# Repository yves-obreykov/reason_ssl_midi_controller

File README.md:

# Reason SSL midi-controller
This project aims to design a custom Midi controller for controlling the SSL-mixer (EQ and Compressor) in Reason DAW

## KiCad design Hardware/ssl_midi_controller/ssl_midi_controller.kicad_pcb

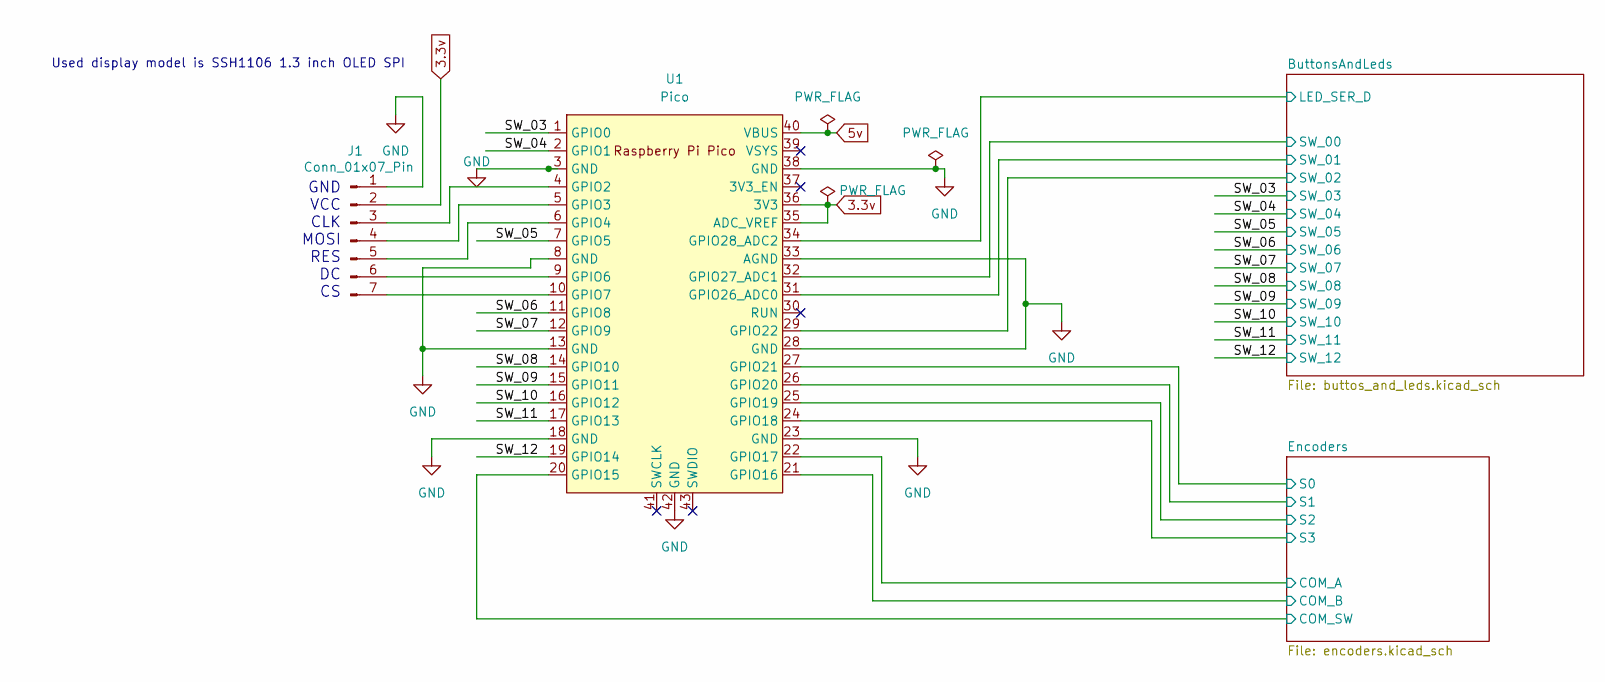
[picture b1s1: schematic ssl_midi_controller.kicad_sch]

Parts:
J1: Conn_01x07_Pin; PinHeader_1x07_P2.54mm_Vertical
U1: Pico; RaspberryPi_Pico_Common_THT

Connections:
3.3v: J1.2, U1.35 (ADC_VREF), U1.36 (3V3); also elsewhere on the board
5v: U1.40 (VBUS); also elsewhere on the board
/ButtonsAndLeds/LED_SER_D: U1.34 (GPIO28_ADC2); also elsewhere on the board
/ButtonsAndLeds/SW_00: U1.32 (GPIO27_ADC1); also elsewhere on the board
/ButtonsAndLeds/SW_01: U1.31 (GPIO26_ADC0); also elsewhere on the board
/ButtonsAndLeds/SW_02: U1.29 (GPIO22); also elsewhere on the board
/Encoders/COM_A: U1.22 (GPIO17); also elsewhere on the board
/Encoders/COM_B: U1.21 (GPIO16); also elsewhere on the board
/Encoders/COM_SW: U1.20 (GPIO15); also elsewhere on the board
/Encoders/S0: U1.27 (GPIO21); also elsewhere on the board
/Encoders/S1: U1.26 (GPIO20); also elsewhere on the board
/Encoders/S2: U1.25 (GPIO19); also elsewhere on the board
/Encoders/S3: U1.24 (GPIO18); also elsewhere on the board
/SW_03: U1.1 (GPIO0); also elsewhere on the board
/SW_04: U1.2 (GPIO1); also elsewhere on the board
/SW_05: U1.7 (GPIO5); also elsewhere on the board
/SW_06: U1.11 (GPIO8); also elsewhere on the board
/SW_07: U1.12 (GPIO9); also elsewhere on the board
/SW_08: U1.14 (GPIO10); also elsewhere on the board
/SW_09: U1.15 (GPIO11); also elsewhere on the board
/SW_10: U1.16 (GPIO12); also elsewhere on the board
/SW_11: U1.17 (GPIO13); also elsewhere on the board
/SW_12: U1.19 (GPIO14); also elsewhere on the board
GND: J1.1, U1.3 (GND), U1.8 (GND), U1.13 (GND), U1.18 (GND), U1.23 (GND), U1.28 (GND), U1.33 (AGND), U1.38 (GND), U1.42 (GND); also elsewhere on the board
unnamed: J1.3, U1.4 (GPIO2)
unnamed: J1.4, U1.5 (GPIO3)
unnamed: J1.5, U1.6 (GPIO4)
unnamed: J1.6, U1.9 (GPIO6)
unnamed: J1.7, U1.10 (GPIO7)

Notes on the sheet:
Used display model is SSH1106 1.3 inch OLED SPI
GND VCC CLK MOSI RES DC CS

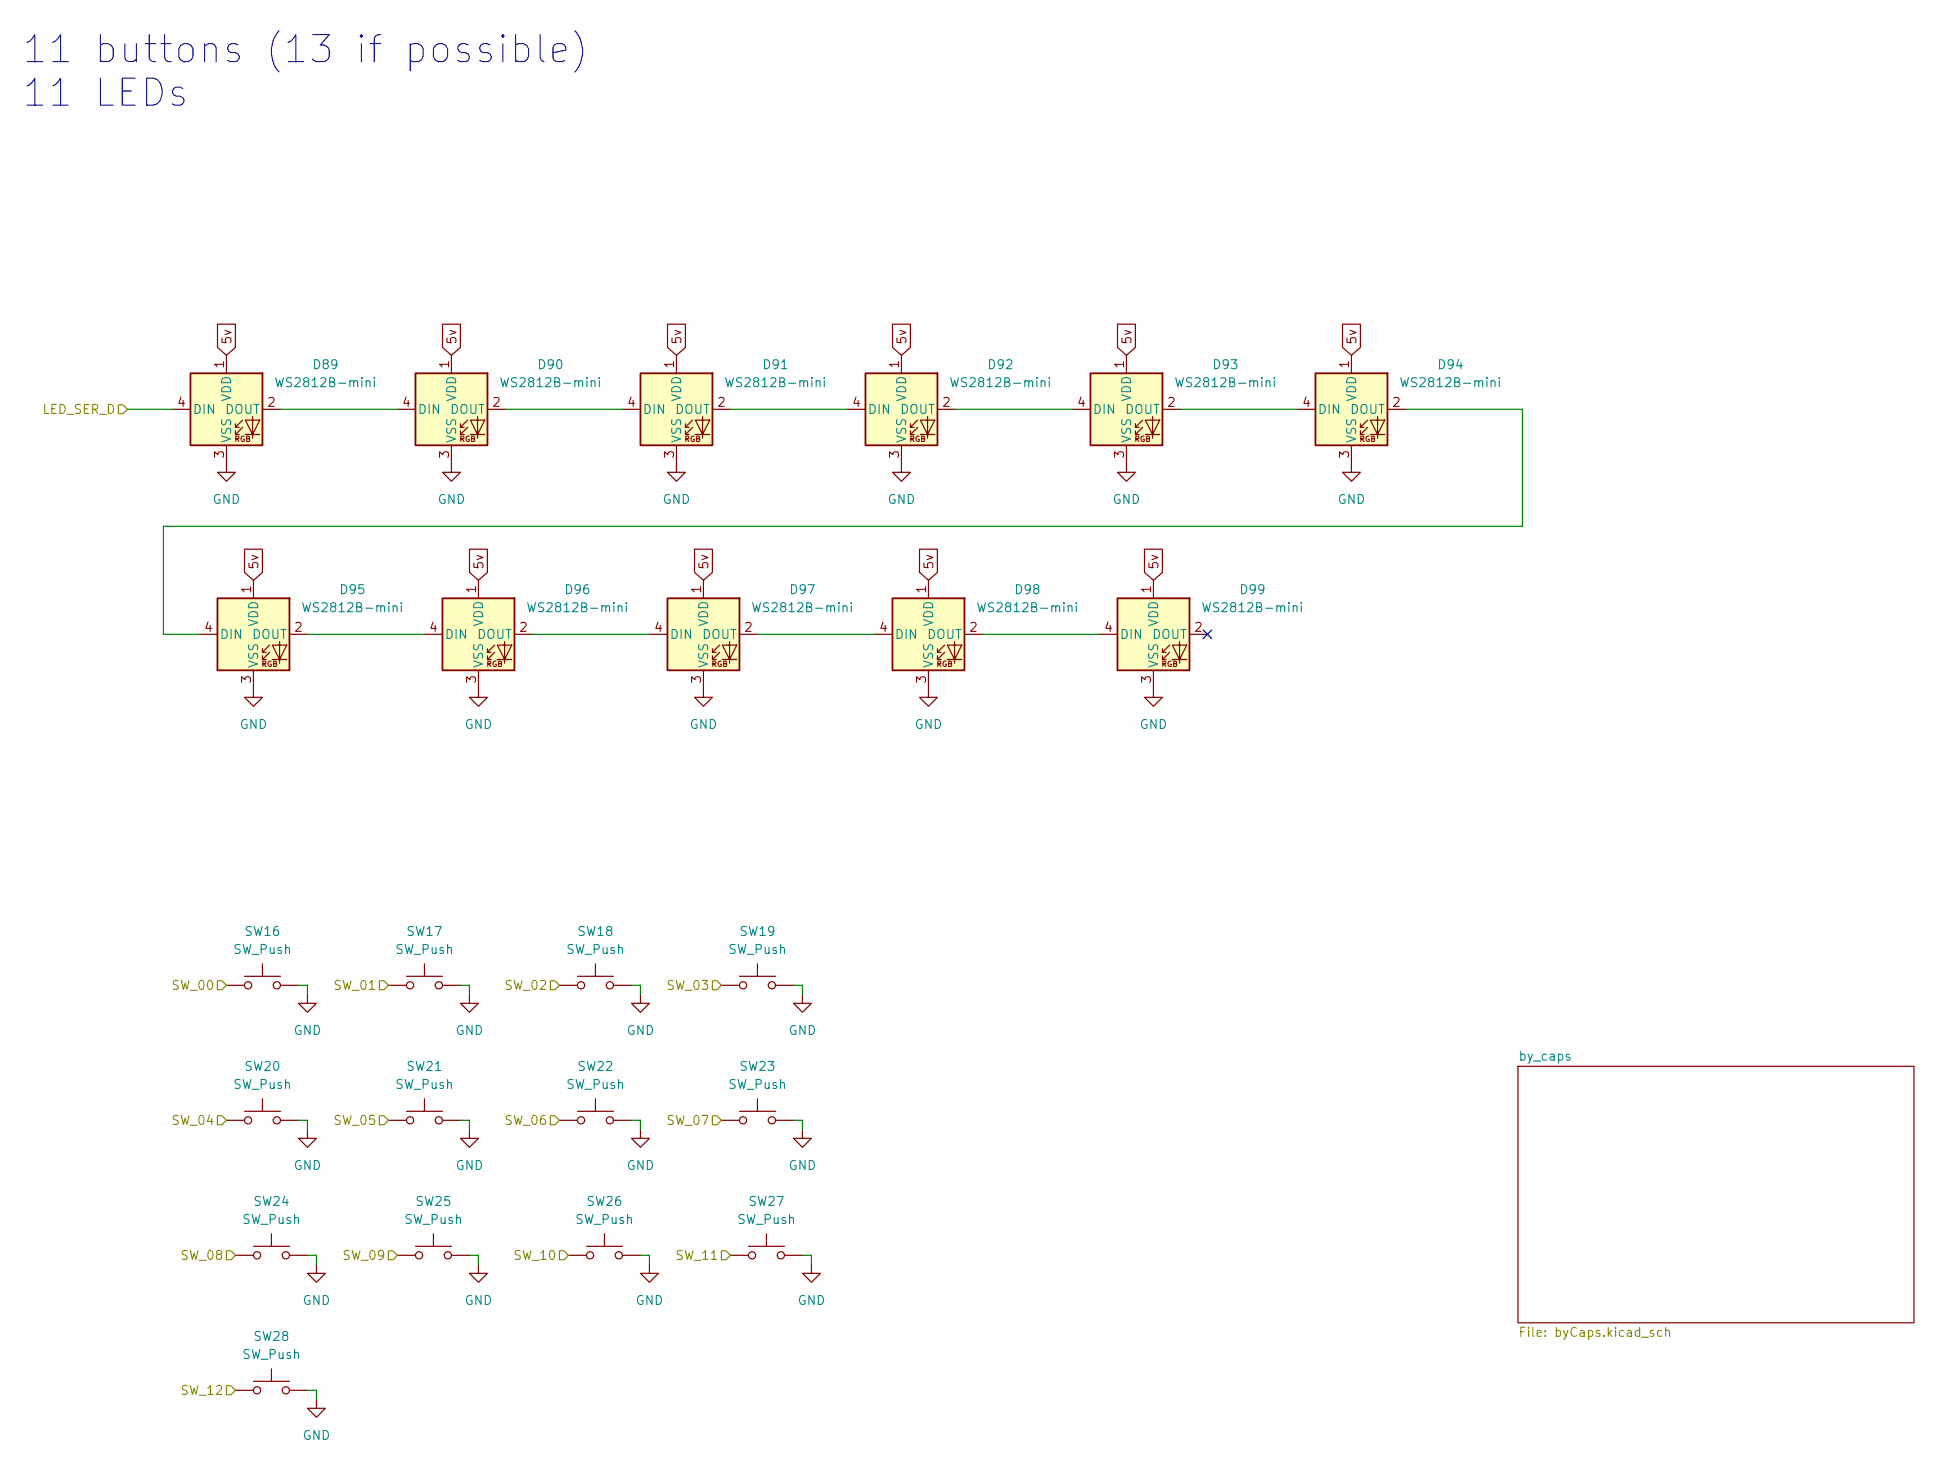
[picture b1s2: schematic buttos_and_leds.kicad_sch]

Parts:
D89, D90, D91, D92, D93, D94, D95, D96, D97, D98, D99: WS2812B-mini; LED_WS2812B-Mini_PLCC4_3.5x3.5mm
SW16, SW17, SW18, SW19, SW20, SW21, SW22, SW23, SW24, SW25, SW26, SW27, SW28: SW_Push; SW_PUSH_6mm_H5mm

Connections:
5v: D89.1 (VDD), D90.1 (VDD), D91.1 (VDD), D92.1 (VDD), D93.1 (VDD), D94.1 (VDD), D95.1 (VDD), D96.1 (VDD), D97.1 (VDD), D98.1 (VDD), D99.1 (VDD); also elsewhere on the board
/ButtonsAndLeds/LED_SER_D: D89.4 (DIN); also elsewhere on the board
/ButtonsAndLeds/SW_00: SW16.1; also elsewhere on the board
/ButtonsAndLeds/SW_01: SW17.1; also elsewhere on the board
/ButtonsAndLeds/SW_02: SW18.1; also elsewhere on the board
/SW_03: SW19.1; also elsewhere on the board
/SW_04: SW20.1; also elsewhere on the board
/SW_05: SW21.1; also elsewhere on the board
/SW_06: SW22.1; also elsewhere on the board
/SW_07: SW23.1; also elsewhere on the board
/SW_08: SW24.1; also elsewhere on the board
/SW_09: SW25.1; also elsewhere on the board
/SW_10: SW26.1; also elsewhere on the board
/SW_11: SW27.1; also elsewhere on the board
/SW_12: SW28.1; also elsewhere on the board
GND: D89.3 (VSS), D90.3 (VSS), D91.3 (VSS), D92.3 (VSS), D93.3 (VSS), D94.3 (VSS), D95.3 (VSS), D96.3 (VSS), D97.3 (VSS), D98.3 (VSS), D99.3 (VSS), SW16.2, SW17.2, SW18.2, SW19.2, SW20.2, SW21.2, SW22.2, SW23.2, SW24.2, SW25.2, SW26.2, SW27.2, SW28.2; also elsewhere on the board
unnamed: D89.2 (DOUT), D90.4 (DIN)
unnamed: D90.2 (DOUT), D91.4 (DIN)
unnamed: D91.2 (DOUT), D92.4 (DIN)
unnamed: D92.2 (DOUT), D93.4 (DIN)
unnamed: D93.2 (DOUT), D94.4 (DIN)
unnamed: D94.2 (DOUT), D95.4 (DIN)
unnamed: D95.2 (DOUT), D96.4 (DIN)
unnamed: D96.2 (DOUT), D97.4 (DIN)
unnamed: D97.2 (DOUT), D98.4 (DIN)
unnamed: D98.2 (DOUT), D99.4 (DIN)

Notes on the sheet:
11 buttons (13 if possible) 11 LEDs

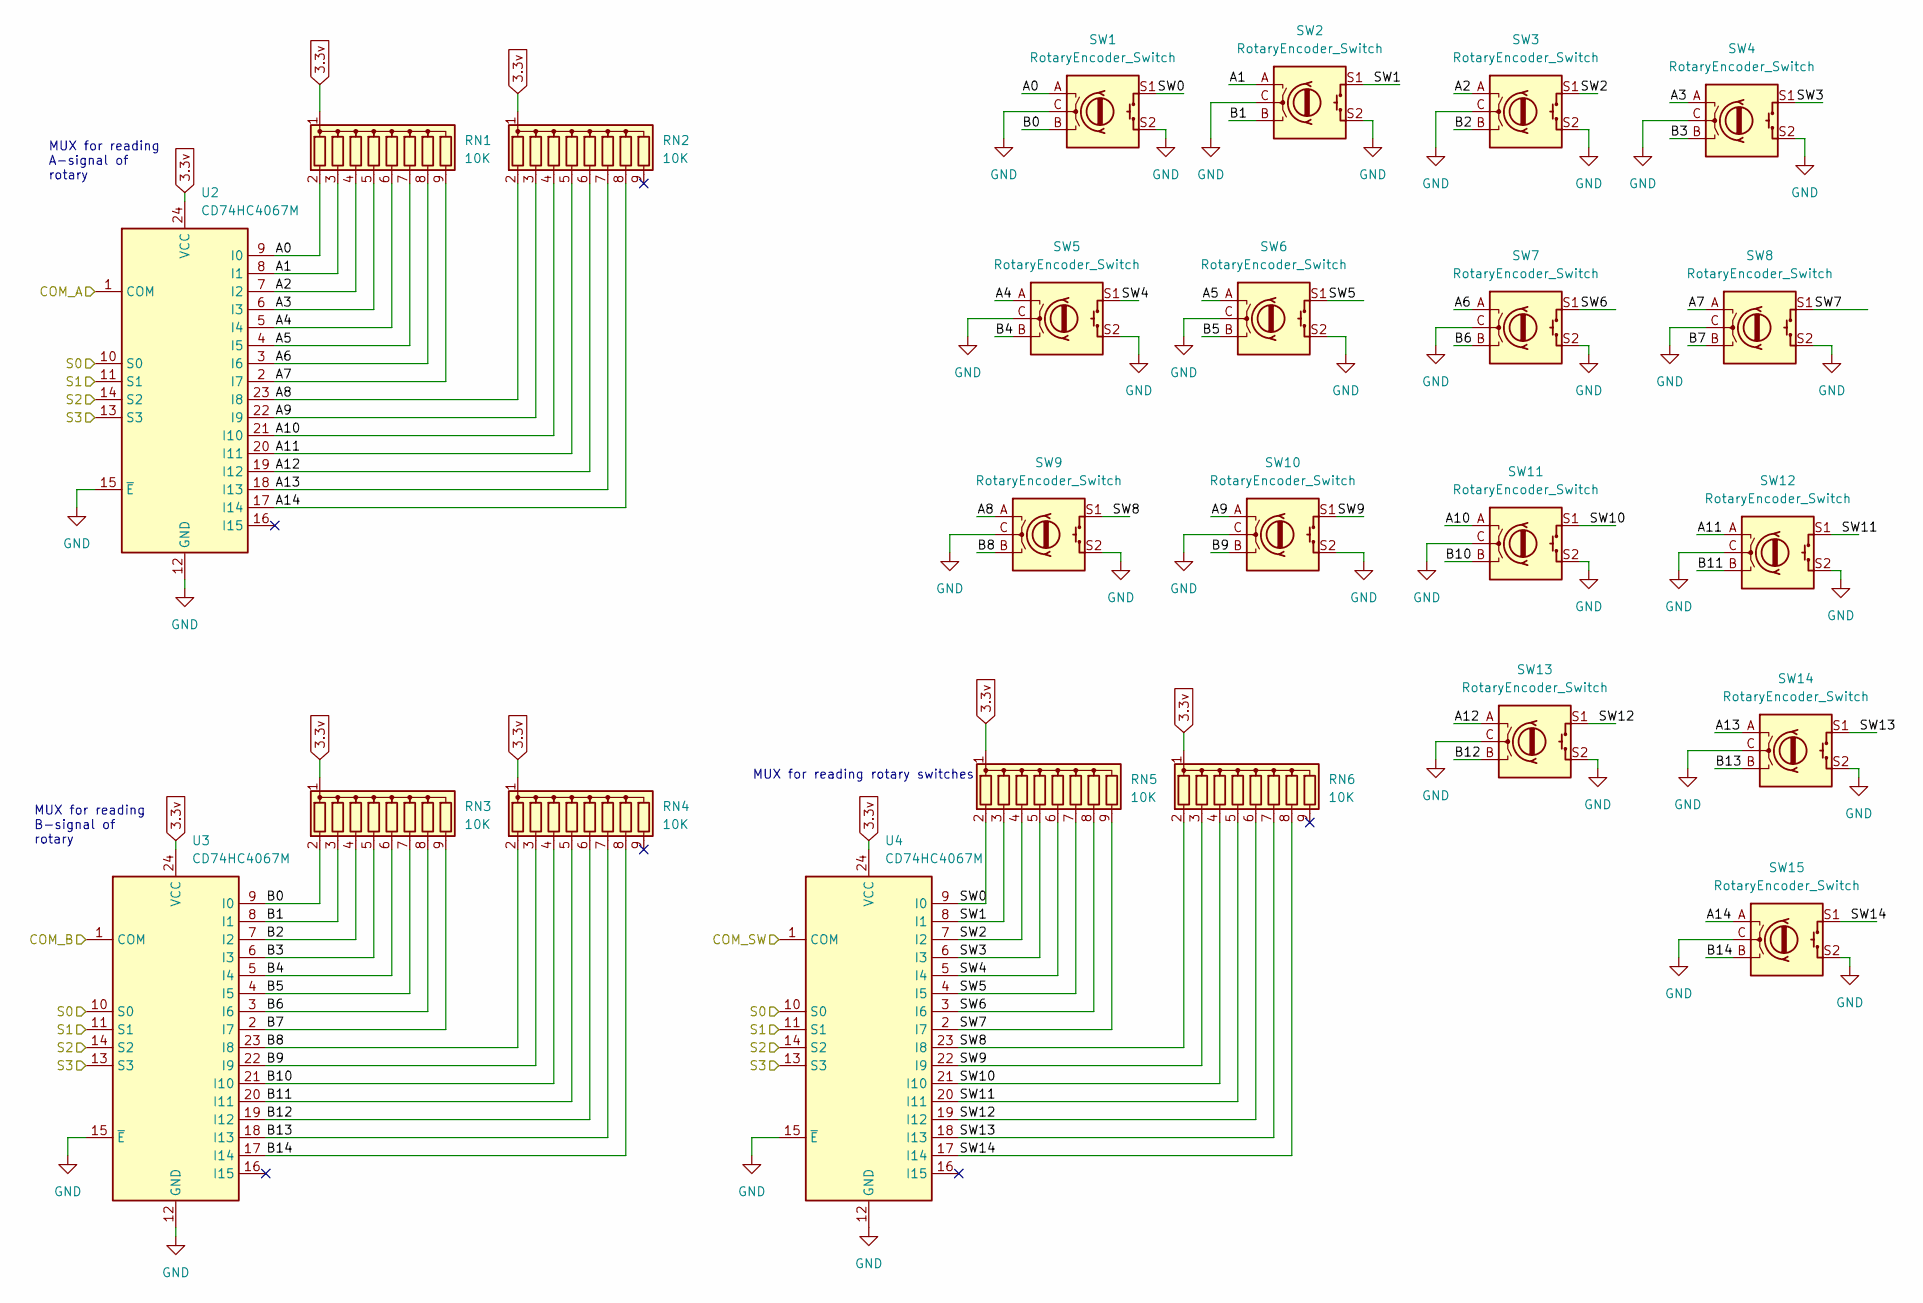
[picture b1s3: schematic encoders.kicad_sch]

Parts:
RN1, RN2, RN3, RN4, RN5, RN6: 10K; R_Array_SIP9
SW1, SW2, SW3, SW4, SW5, SW6, SW7, SW8, SW9, SW10, SW11, SW12, SW13, SW14, SW15: RotaryEncoder_Switch; RotaryEncoder_Alps_EC11E-Switch_Vertical_H20mm_MountingHoles
U2, U3, U4: CD74HC4067M; SOIC-24W_7.5x15.4mm_P1.27mm

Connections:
3.3v: RN1.1 (common), RN2.1 (common), RN3.1 (common), RN4.1 (common), RN5.1 (common), RN6.1 (common), U2.24 (VCC), U3.24 (VCC), U4.24 (VCC); also elsewhere on the board
/Encoders/A0: RN1.2 (R1), SW1.A, U2.9 (I0)
/Encoders/A1: RN1.3 (R2), SW2.A, U2.8 (I1)
/Encoders/A2: RN1.4 (R3), SW3.A, U2.7 (I2)
/Encoders/A3: RN1.5 (R4), SW4.A, U2.6 (I3)
/Encoders/A4: RN1.6 (R5), SW5.A, U2.5 (I4)
/Encoders/A5: RN1.7 (R6), SW6.A, U2.4 (I5)
/Encoders/A6: RN1.8 (R7), SW7.A, U2.3 (I6)
/Encoders/A7: RN1.9 (R8), SW8.A, U2.2 (I7)
/Encoders/A8: RN2.2 (R1), SW9.A, U2.23 (I8)
/Encoders/A9: RN2.3 (R2), SW10.A, U2.22 (I9)
/Encoders/A10: RN2.4 (R3), SW11.A, U2.21 (I10)
/Encoders/A11: RN2.5 (R4), SW12.A, U2.20 (I11)
/Encoders/A12: RN2.6 (R5), SW13.A, U2.19 (I12)
/Encoders/A13: RN2.7 (R6), SW14.A, U2.18 (I13)
/Encoders/A14: RN2.8 (R7), SW15.A, U2.17 (I14)
/Encoders/B0: RN3.2 (R1), SW1.B, U3.9 (I0)
/Encoders/B1: RN3.3 (R2), SW2.B, U3.8 (I1)
/Encoders/B2: RN3.4 (R3), SW3.B, U3.7 (I2)
/Encoders/B3: RN3.5 (R4), SW4.B, U3.6 (I3)
/Encoders/B4: RN3.6 (R5), SW5.B, U3.5 (I4)
/Encoders/B5: RN3.7 (R6), SW6.B, U3.4 (I5)
/Encoders/B6: RN3.8 (R7), SW7.B, U3.3 (I6)
/Encoders/B7: RN3.9 (R8), SW8.B, U3.2 (I7)
/Encoders/B8: RN4.2 (R1), SW9.B, U3.23 (I8)
/Encoders/B9: RN4.3 (R2), SW10.B, U3.22 (I9)
/Encoders/B10: RN4.4 (R3), SW11.B, U3.21 (I10)
/Encoders/B11: RN4.5 (R4), SW12.B, U3.20 (I11)
/Encoders/B12: RN4.6 (R5), SW13.B, U3.19 (I12)
/Encoders/B13: RN4.7 (R6), SW14.B, U3.18 (I13)
/Encoders/B14: RN4.8 (R7), SW15.B, U3.17 (I14)
/Encoders/COM_A: U2.1 (COM); also elsewhere on the board
/Encoders/COM_B: U3.1 (COM); also elsewhere on the board
/Encoders/COM_SW: U4.1 (COM); also elsewhere on the board
/Encoders/S0: U2.10 (S0), U3.10 (S0), U4.10 (S0); also elsewhere on the board
/Encoders/S1: U2.11 (S1), U3.11 (S1), U4.11 (S1); also elsewhere on the board
/Encoders/S2: U2.14 (S2), U3.14 (S2), U4.14 (S2); also elsewhere on the board
/Encoders/S3: U2.13 (S3), U3.13 (S3), U4.13 (S3); also elsewhere on the board
/Encoders/SW0: RN5.2 (R1), SW1.S1, U4.9 (I0)
/Encoders/SW1: RN5.3 (R2), SW2.S1, U4.8 (I1)
/Encoders/SW2: RN5.4 (R3), SW3.S1, U4.7 (I2)
/Encoders/SW3: RN5.5 (R4), SW4.S1, U4.6 (I3)
/Encoders/SW4: RN5.6 (R5), SW5.S1, U4.5 (I4)
/Encoders/SW5: RN5.7 (R6), SW6.S1, U4.4 (I5)
/Encoders/SW6: RN5.8 (R7), SW7.S1, U4.3 (I6)
/Encoders/SW7: RN5.9 (R8), SW8.S1, U4.2 (I7)
/Encoders/SW8: RN6.2 (R1), SW9.S1, U4.23 (I8)
/Encoders/SW9: RN6.3 (R2), SW10.S1, U4.22 (I9)
/Encoders/SW10: RN6.4 (R3), SW11.S1, U4.21 (I10)
/Encoders/SW11: RN6.5 (R4), SW12.S1, U4.20 (I11)
/Encoders/SW12: RN6.6 (R5), SW13.S1, U4.19 (I12)
/Encoders/SW13: RN6.7 (R6), SW14.S1, U4.18 (I13)
/Encoders/SW14: RN6.8 (R7), SW15.S1, U4.17 (I14)
GND: SW1.C, SW1.S2, SW2.C, SW2.S2, SW3.C, SW3.S2, SW4.C, SW4.S2, SW5.C, SW5.S2, SW6.C, SW6.S2, SW7.C, SW7.S2, SW8.C, SW8.S2, SW9.C, SW9.S2, SW10.C, SW10.S2, SW11.C, SW11.S2, SW12.C, SW12.S2, SW13.C, SW13.S2, SW14.C, SW14.S2, SW15.C, SW15.S2, U2.12 (GND), U2.15 (~E), U3.12 (GND), U3.15 (~E), U4.12 (GND), U4.15 (~E); also elsewhere on the board

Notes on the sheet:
MUX for reading rotary switches
MUX for reading B-signal of rotary
MUX for reading A-signal of rotary

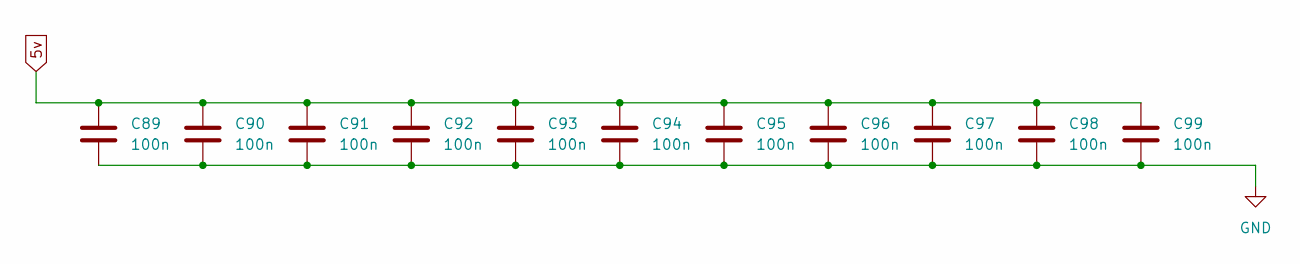
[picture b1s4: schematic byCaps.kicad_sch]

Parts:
C89, C90, C91, C92, C93, C94, C95, C96, C97, C98, C99: 100n; C_0805_2012Metric_Pad1.18x1.45mm_HandSolder

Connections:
5v: C89.1, C90.1, C91.1, C92.1, C93.1, C94.1, C95.1, C96.1, C97.1, C98.1, C99.1; also elsewhere on the board
GND: C89.2, C90.2, C91.2, C92.2, C93.2, C94.2, C95.2, C96.2, C97.2, C98.2, C99.2; also elsewhere on the board

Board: 2 copper layers, 61 parts (0 on the bottom side), 84 nets, no tracks yet.

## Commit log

2025-05-31 Schematic done
